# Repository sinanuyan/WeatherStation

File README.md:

# WeatherStation
Opensource Weather Station with OpenWeather

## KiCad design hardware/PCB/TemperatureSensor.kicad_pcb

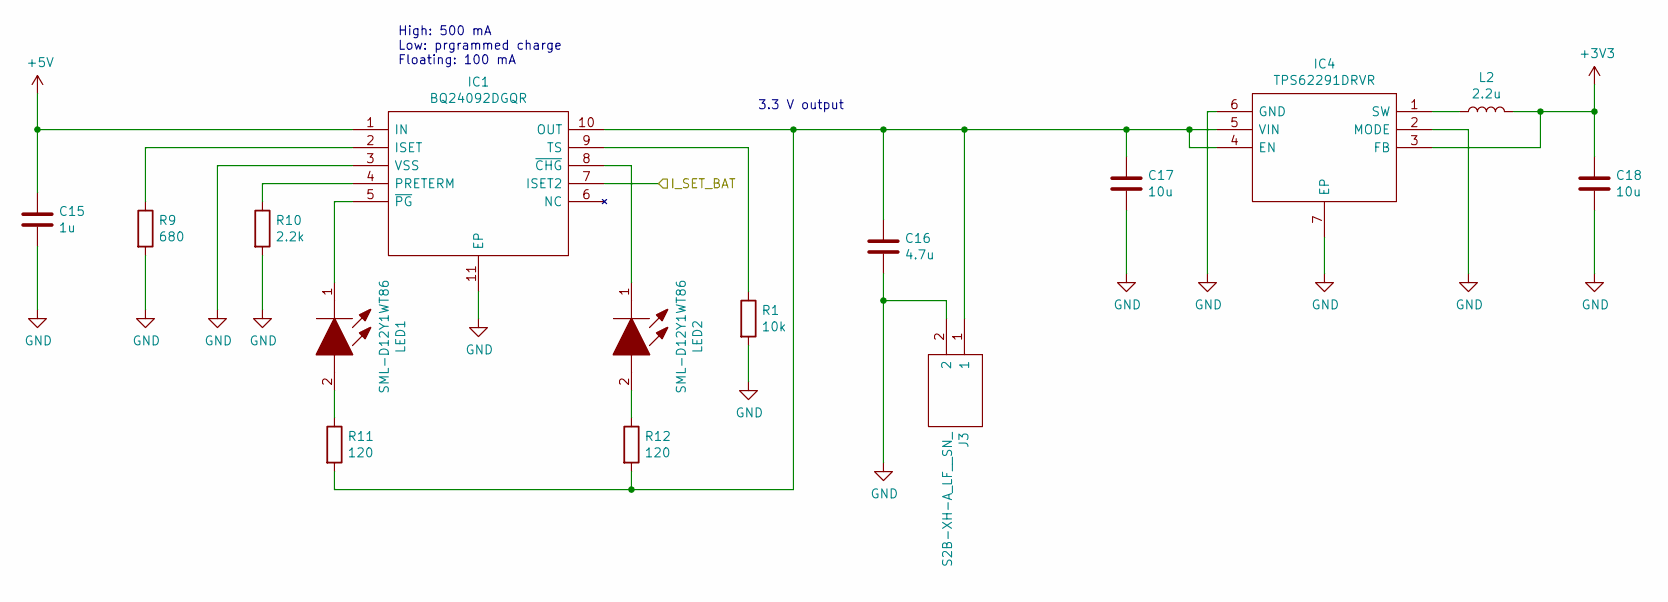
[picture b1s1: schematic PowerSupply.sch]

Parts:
C15: 1u; C_0603_1608Metric
C16: 4.7u; C_0603_1608Metric
C17, C18: 10u; C_0603_1608Metric
IC1: BQ24092DGQR; SOP50P490X110-11N; Mouser Part Number 595-BQ24092DGQR
IC4: TPS62291DRVR; SON65P200X200X80-7N; Mouser Part Number 595-TPS62291DRVR
J3: S2B-XH-A_LF__SN_; SHDRRA2W80P0X250_1X2_740X1150X610P; Manufacturer_Part_Number S2B-XH-A(LF)(SN)
L2: 2.2u; L_Coilcraft_LPS4018; Mouser Part Number 994-LPS4018-222MRB
LED1, LED2: SML-D12Y1WT86; LEDC1608X55N; Mouser Part Number 755-SML-D12Y1WT86
R1: 10k; R_0603_1608Metric
R9: 680; R_0603_1608Metric
R10: 2.2k; R_0603_1608Metric
R11, R12: 120; R_0603_1608Metric

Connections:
+5V: C15.1, IC1.1 (IN); also elsewhere on the board
/ESP32/BAT_PWR: IC1.7 (ISET2); also elsewhere on the board
GND: C15.2, C16.2, C17.2, C18.2, IC1.3 (VSS), IC1.11 (EP), IC4.2 (MODE), IC4.6 (GND), IC4.7 (EP), J3.2, R1.2, R9.2, R10.2; also elsewhere on the board
unnamed: C16.1, C17.1, IC1.10 (OUT), IC4.4 (EN), IC4.5 (VIN), J3.1, R11.2, R12.2
unnamed: IC1.2 (ISET), R9.1
unnamed: IC1.4 (PRETERM), R10.1
unnamed: IC1.5 (~PG), LED1.1
unnamed: IC1.8 (~CHG), LED2.1
unnamed: IC1.9 (TS), R1.1
unnamed: IC4.1 (SW), L2.1
unnamed: LED1.2, R11.1
unnamed: LED2.2, R12.1

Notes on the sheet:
3.3 V output
High: 500 mA Low: prgrammed charge Floating: 100 mA

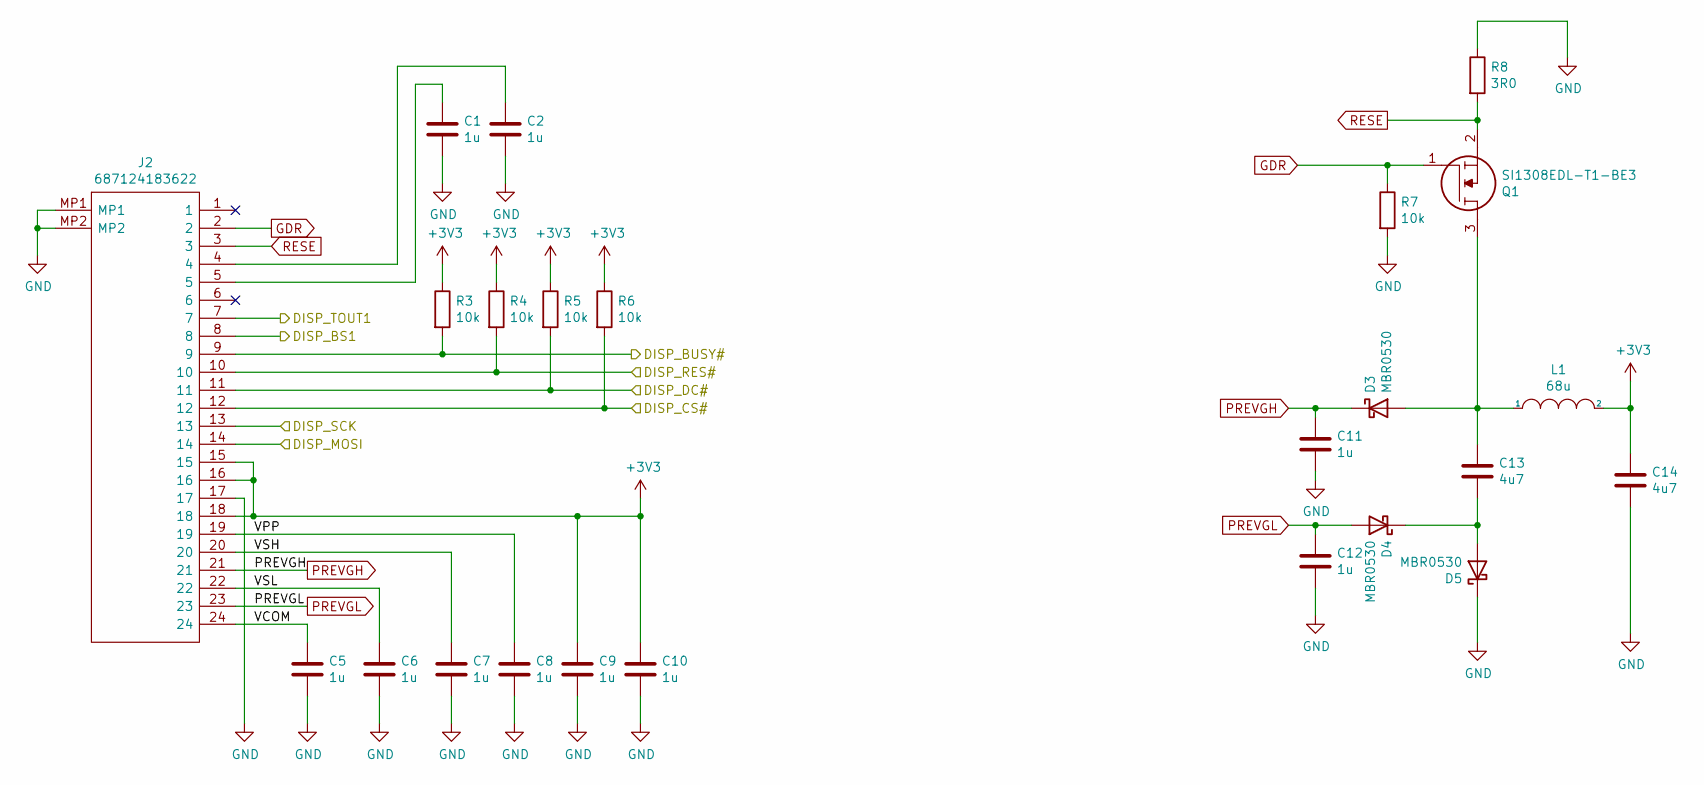
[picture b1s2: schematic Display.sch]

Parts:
C1, C2, C5, C6, C7, C8, C9, C10, C11, C12: 1u; C_0603_1608Metric
C13, C14: 4u7; C_0603_1608Metric
D3, D4, D5: MBR0530; D_SOD-123
J2: 687124183622; Mouser Part Number 710-687124183622
L1: 68u; L_0805_2012Metric
Q1: SI1308EDL-T1-BE3; SOT65P210X110-3N; Manufacturer_Part_Number SI1308EDL-T1-BE3
R3, R4, R5, R6, R7: 10k; R_0603_1608Metric
R8: 3R0; R_0603_1608Metric

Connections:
/Display/DISP_BS1: J2.8; also elsewhere on the board
/Display/DISP_MOSI: J2.14; also elsewhere on the board
/Display/DISP_TOUT1: J2.7; also elsewhere on the board
/Display/VCOM: C5.1, J2.24
/Display/VPP: C8.1, J2.19
/Display/VSH: C7.1, J2.20
/Display/VSL: C6.1, J2.22
/ESP32/DISP_BUSY: J2.9, R3.2; also elsewhere on the board
/ESP32/DISP_CLK: J2.13; also elsewhere on the board
/ESP32/DISP_CS: J2.12, R6.2; also elsewhere on the board
/ESP32/DISP_DC: J2.11, R5.2; also elsewhere on the board
/ESP32/DISP_RES: J2.10, R4.2; also elsewhere on the board
GDR: J2.2, Q1.1, R7.1
GND: C1.2, C2.2, C5.2, C6.2, C7.2, C8.2, C9.2, C10.2, C11.2, C12.2, C14.2, D5.1 (K), J2.17, J2.MP1, J2.MP2, R7.2, R8.1; also elsewhere on the board
unnamed: C1.1, J2.5
unnamed: C2.1, J2.4
unnamed: C13.1, D3.2 (A), L1.1, Q1.3
unnamed: C13.2, D4.1 (K), D5.2 (A)
PREVGH: C11.1, D3.1 (K), J2.21
PREVGL: C12.1, D4.2 (A), J2.23
RESE: J2.3, Q1.2, R8.2

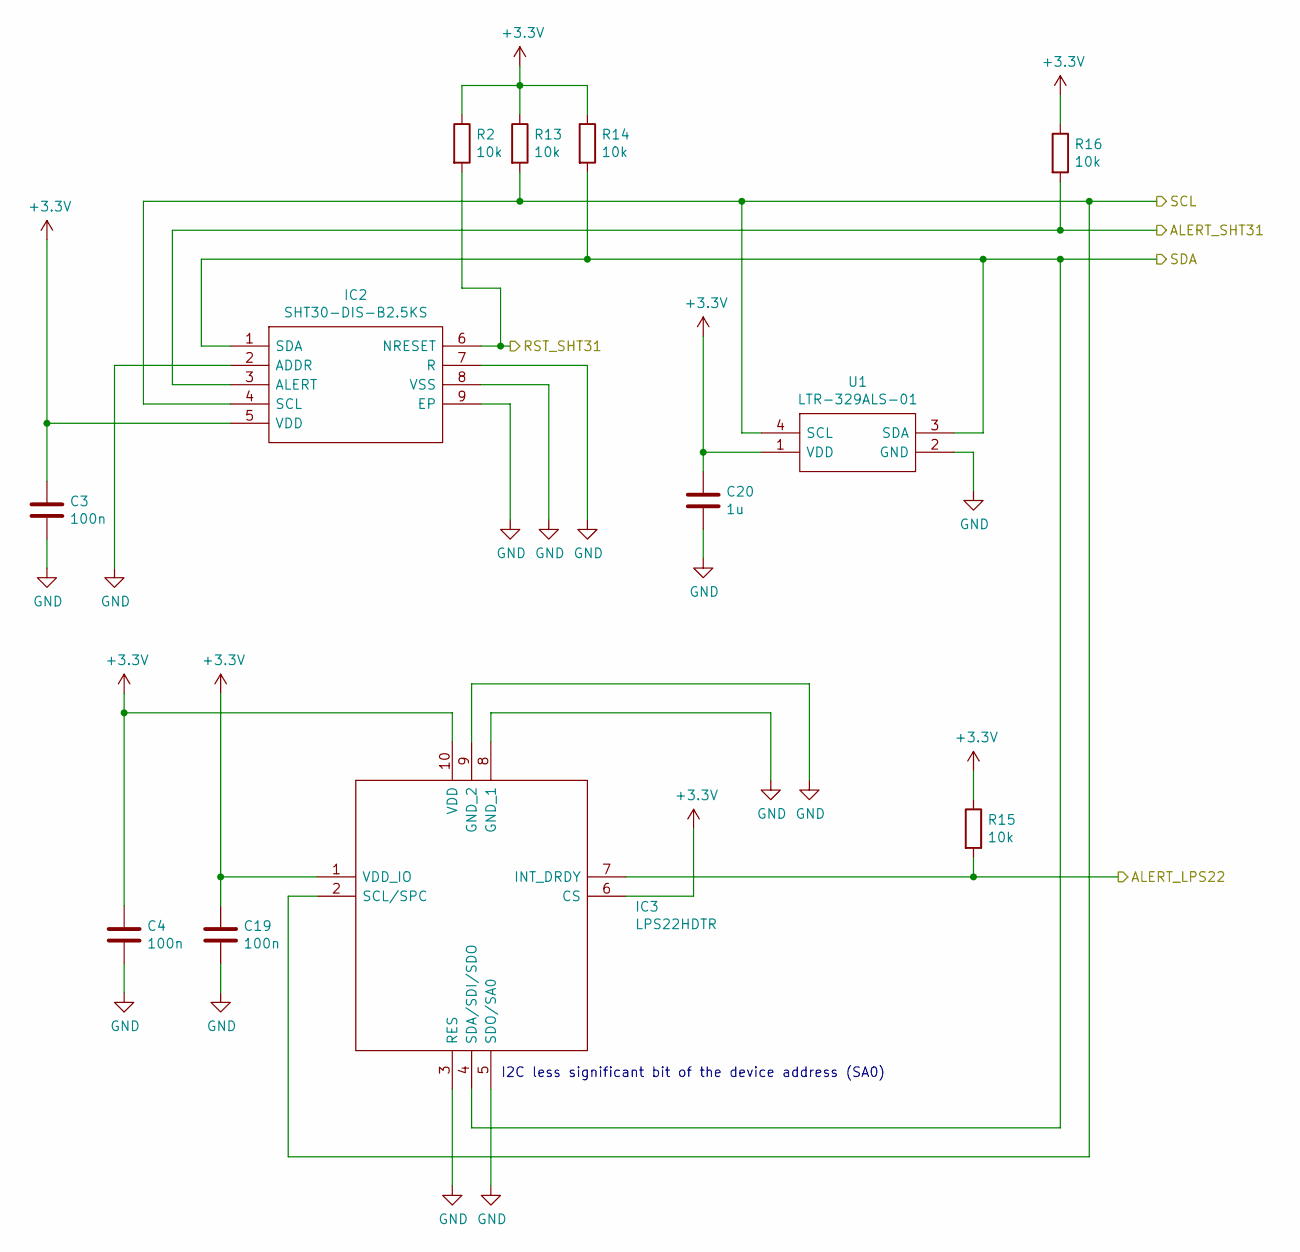
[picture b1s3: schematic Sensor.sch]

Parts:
C3, C4, C19: 100n; C_0603_1608Metric
C20: 1u; C_0603_1608Metric
IC2: SHT30-DIS-B2.5KS; SHT30DISB25KS; Manufacturer_Part_Number SHT30-DIS-B2.5KS
IC3: LPS22HDTR; Mouser Part Number 511-LPS22HDTR
R2, R13, R14, R15, R16: 10k; R_0603_1608Metric
U1: LTR-329ALS-01; LTR329ALS01; Mouser Part Number 859-LTR-329ALS-01

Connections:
/ESP32/I2C_SCL: IC2.4 (SCL), IC3.2 (SCL/SPC), R13.2, U1.4 (SCL); also elsewhere on the board
/ESP32/I2C_SDA: IC2.1 (SDA), IC3.4 (SDA/SDI/SDO), R14.2, U1.3 (SDA); also elsewhere on the board
/Sensor/ALERT_LPS22: IC3.7 (INT_DRDY), R15.2
/Sensor/ALERT_SHT31: IC2.3 (ALERT), R16.2
/Sensor/RST_SHT31: IC2.6 (NRESET), R2.2; also elsewhere on the board
GND: C3.2, C4.2, C19.2, C20.2, IC2.2 (ADDR), IC2.7 (R), IC2.8 (VSS), IC2.9 (EP), IC3.3 (RES), IC3.5 (SDO/SA0), IC3.8 (GND_1), IC3.9 (GND_2), U1.2 (GND); also elsewhere on the board

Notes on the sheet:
I2C less significant bit of the device address (SA0)

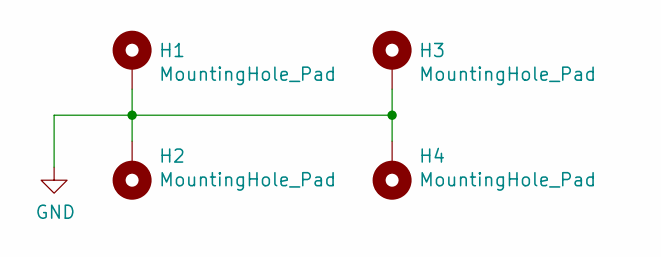
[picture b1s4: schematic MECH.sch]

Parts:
H1, H2, H3, H4: MountingHole_Pad; MountingHole_2.5mm

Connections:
GND: H1.1, H2.1, H3.1, H4.1; also elsewhere on the board

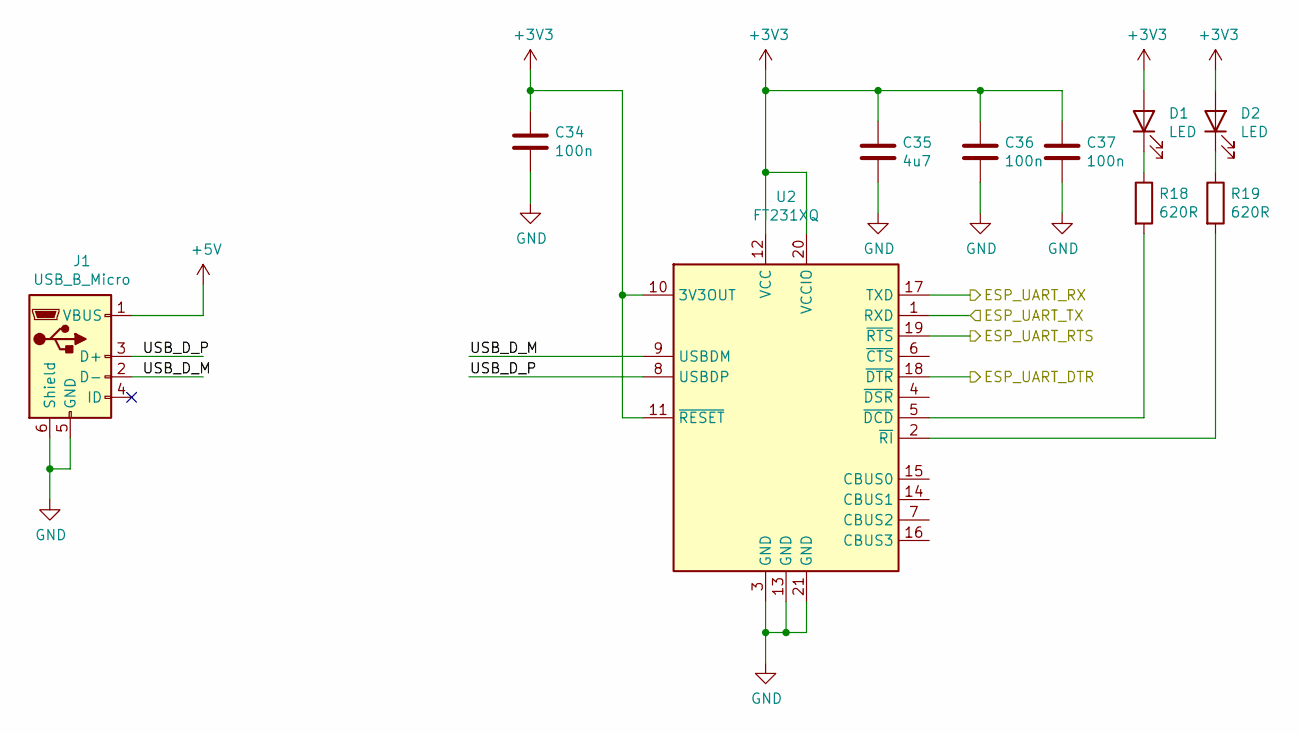
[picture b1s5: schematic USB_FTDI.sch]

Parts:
C34, C36, C37: 100n; C_0603_1608Metric
C35: 4u7; C_0603_1608Metric
D1, D2: LED; LED_0603_1608Metric
J1: USB_B_Micro; USB_Micro-B_Amphenol_10118194_Horizontal
R18, R19: 620R; R_0603_1608Metric
U2: FT231XQ; QFN-20-1EP_4x4mm_P0.5mm_EP2.5x2.5mm

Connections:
+5V: J1.1 (VBUS); also elsewhere on the board
/USB FTDI/ESP_UART_DTR: U2.18 (~DTR); also elsewhere on the board
/USB FTDI/ESP_UART_RTS: U2.19 (~RTS); also elsewhere on the board
/USB FTDI/ESP_UART_RX: U2.17 (TXD); also elsewhere on the board
/USB FTDI/ESP_UART_TX: U2.1 (RXD); also elsewhere on the board
/USB FTDI/USB_D_M: J1.2 (D-), U2.9 (USBDM)
/USB FTDI/USB_D_P: J1.3 (D+), U2.8 (USBDP)
GND: C34.2, C35.2, C36.2, C37.2, J1.5 (GND), J1.6 (Shield), U2.3 (GND), U2.13 (GND), U2.21 (GND); also elsewhere on the board
unnamed: D1.1 (K), R18.1
unnamed: D2.1 (K), R19.1
unnamed: R18.2, U2.5 (~DCD)
unnamed: R19.2, U2.2 (~RI)

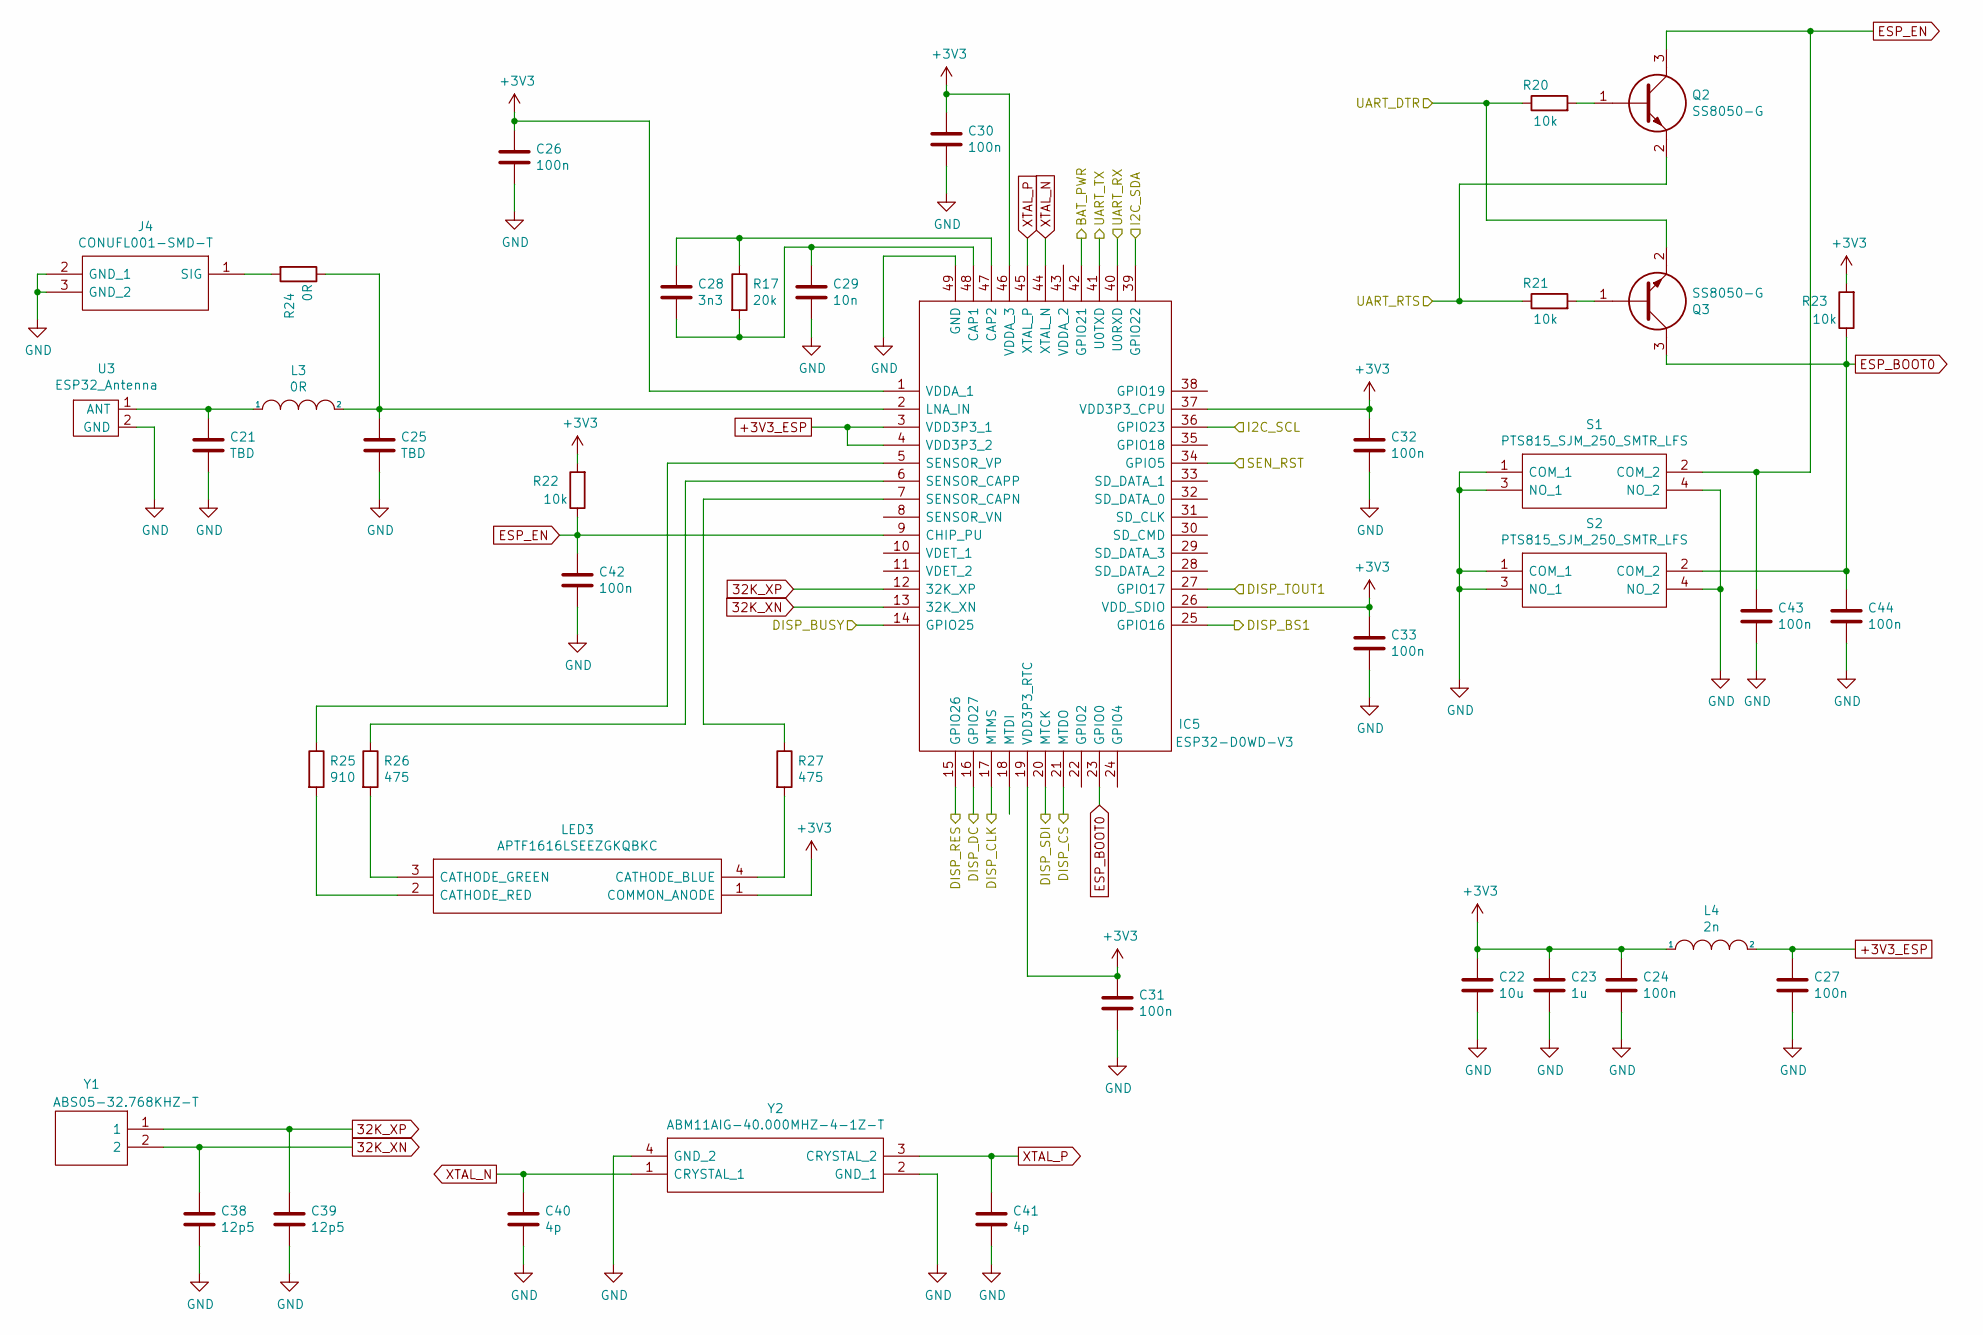
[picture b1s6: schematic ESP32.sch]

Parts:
C21, C25: TBD; C_0603_1608Metric
C22: 10u; C_0603_1608Metric
C23: 1u; C_0603_1608Metric
C24, C26, C27, C30, C31, C32, C33, C42, C43, C44: 100n; C_0603_1608Metric
C28: 3n3; C_0603_1608Metric
C29: 10n; C_0603_1608Metric
C38, C39: 12p5; C_0603_1608Metric
C40, C41: 4p; C_0603_1608Metric
IC5: ESP32-D0WD-V3; QFN35P500X500X90-49N-D; Mouser Part Number 356-ESP32-D0WD-V3
J4: CONUFL001-SMD-T; CONUFL001-SMD; Mouser Part Number 712-CONUFL001-SMD-T
L3: 0R; L_0603_1608Metric
L4: 2n; L_0603_1608Metric
LED3: APTF1616LSEEZGKQBKC; APTF1616SEEZGQBDC; Mouser Part Number 604-APTF1616LSEEZGKQ
Q2, Q3: SS8050-G; SOT95P240X115-3N; Mouser Part Number 750-SS8050-G
R17: 20k; R_0603_1608Metric
R20, R21, R22, R23: 10k; R_0603_1608Metric
R24: 0R; R_0603_1608Metric
R25: 910; R_0603_1608Metric
R26, R27: 475; R_0603_1608Metric
S1, S2: PTS815_SJM_250_SMTR_LFS; PTS815SJM250SMTRLFS; Mouser Part Number 611-PTS815SJM250SMTR
U3: ESP32_Antenna; Texas_SWRA117D_2.4GHz_Right
Y1: ABS05-32.768KHZ-T; ABS05; Mouser Part Number 815-ABS05-32.768K-T
Y2: ABM11AIG-40.000MHZ-4-1Z-T; ABM11AIG40000MHZ41ZT; Mouser Part Number 815-M11AIG-40-4-1ZT

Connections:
32K_XN: C38.1, IC5.13 (32K_XN), Y1.2
32K_XP: C39.1, IC5.12 (32K_XP), Y1.1
+3V3_ESP: C27.1, IC5.3 (VDD3P3_1), IC5.4 (VDD3P3_2), L4.2
/Display/DISP_BS1: IC5.25 (GPIO16); also elsewhere on the board
/Display/DISP_MOSI: IC5.20 (MTCK); also elsewhere on the board
/Display/DISP_TOUT1: IC5.27 (GPIO17); also elsewhere on the board
/ESP32/BAT_PWR: IC5.42 (GPIO21); also elsewhere on the board
/ESP32/DISP_BUSY: IC5.14 (GPIO25); also elsewhere on the board
/ESP32/DISP_CLK: IC5.17 (MTMS); also elsewhere on the board
/ESP32/DISP_CS: IC5.21 (MTDO); also elsewhere on the board
/ESP32/DISP_DC: IC5.16 (GPIO27); also elsewhere on the board
/ESP32/DISP_RES: IC5.15 (GPIO26); also elsewhere on the board
/ESP32/I2C_SCL: IC5.36 (GPIO23); also elsewhere on the board
/ESP32/I2C_SDA: IC5.39 (GPIO22); also elsewhere on the board
/Sensor/RST_SHT31: IC5.34 (GPIO5); also elsewhere on the board
/USB FTDI/ESP_UART_DTR: Q3.2, R20.1; also elsewhere on the board
/USB FTDI/ESP_UART_RTS: Q2.2, R21.1; also elsewhere on the board
/USB FTDI/ESP_UART_RX: IC5.40 (U0RXD); also elsewhere on the board
/USB FTDI/ESP_UART_TX: IC5.41 (U0TXD); also elsewhere on the board
ESP_BOOT0: C44.1, IC5.23 (GPIO0), Q3.3, R23.1, S2.2 (COM_2)
ESP_EN: C42.1, C43.1, IC5.9 (CHIP_PU), Q2.3, R22.1, S1.2 (COM_2)
GND: C21.2, C22.2, C23.2, C24.2, C25.2, C26.2, C27.2, C29.2, C30.2, C31.2, C32.2, C33.2, C38.2, C39.2, C40.2, C41.2, C42.2, C43.2, C44.2, IC5.49 (GND), J4.2 (GND_1), J4.3 (GND_2), S1.1 (COM_1), S1.3 (NO_1), S1.4 (NO_2), S2.1 (COM_1), S2.3 (NO_1), S2.4 (NO_2), U3.2 (GND), Y2.2 (GND_1), Y2.4 (GND_2); also elsewhere on the board
unnamed: C21.1, L3.1, U3.1 (ANT)
unnamed: C25.1, IC5.2 (LNA_IN), L3.2, R24.1
unnamed: C28.1, IC5.47 (CAP2), R17.1
unnamed: C28.2, C29.1, IC5.48 (CAP1), R17.2
unnamed: IC5.5 (SENSOR_VP), R25.1
unnamed: IC5.6 (SENSOR_CAPP), R26.1
unnamed: IC5.7 (SENSOR_CAPN), R27.1
unnamed: J4.1 (SIG), R24.2
unnamed: LED3.2 (CATHODE_RED), R25.2
unnamed: LED3.3 (CATHODE_GREEN), R26.2
unnamed: LED3.4 (CATHODE_BLUE), R27.2
unnamed: Q2.1, R20.2
unnamed: Q3.1, R21.2
XTAL_N: C40.1, IC5.44 (XTAL_N), Y2.1 (CRYSTAL_1)
XTAL_P: C41.1, IC5.45 (XTAL_P), Y2.3 (CRYSTAL_2)

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
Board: 2 copper layers, 106 parts (0 on the bottom side), 68 nets, no tracks yet.

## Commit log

2020-11-19 initial KiCAD commit
2020-11-22 Add temperature and ambient light sensor to library
2020-11-22 Update Project Library paths
2020-11-22 Add new sensors to board
2020-11-22 Add datasheets
2020-11-22 add usb and ftdi circuit
2020-11-23 started display circuit
2020-11-25 Add 4 mounting holes with via pads
2020-11-25 Add BQ24092DGQR for LiPo charging
2020-11-25 Added battery connector
2020-11-25 edited display circuit
2020-11-26 Add TPS62290DRV to PowerSupply
2020-11-28 complete display circuit
2020-11-28 change power out to 3V3
2020-11-28 add ESP32 and Sensor Sheet
2020-11-28 started ESP32 Schematic
2020-11-29 Complete Sensor schematic
2020-11-29 Add LPS22HD pressure sensor
2020-12-13 add e ink datasheet
2020-12-13 add 10k pull up
2020-12-27 add mechannical and usb ftdi sheet
2020-12-27 corretcted usb plus minus connection
2020-12-27 add 32khz crystal for rtc
2020-12-27 add ESP32 antenna
2020-12-27 add inductor footprint LPS4018
2020-12-27 corrected power supply schematic
2020-12-27 add 40 MHz crystal
2020-12-27 changed FTDI chip to full handshake chip
2020-12-27 changed to dtr
2020-12-27 add ESP32 bootloader circuit
2020-12-27 add enable and boot0 buttons
2020-12-27 complete bootloader circuit
2020-12-27 updated pcb
2020-12-29 Add ABS05-32.768KHZ-T symbol and footprint
2020-12-29 Remove custom libraries
2020-12-29 Use added ABS05 symbol and footprint form project library
2020-12-29 Remove dublicated symbol
2020-12-29 Connect ESP32 pins
2020-12-29 Connect Display
2020-12-30 correctrts, dtr connection, change spi connections, complete display connection
2021-01-17 Added debug led fixed #1
2021-01-17 add ufl connector
2021-01-19 Order parts in groups
2021-01-19 Sort components
2021-02-13 component placement done
